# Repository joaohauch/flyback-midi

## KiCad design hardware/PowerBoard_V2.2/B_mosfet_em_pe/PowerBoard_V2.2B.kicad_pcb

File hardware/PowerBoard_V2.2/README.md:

# PowerBoard V2.2: placa de potência fresada (face simples)

É a PowerBoard V2.1 (totem pole) com as correções da V3.6, montada no desenho da PowerBoard V3 do EasyEDA:

- o tamanho é o mesmo, 85,2 × 39,5 mm;
- as peças de potência estão nas mesmas posições;
- saíram o FOD3184, o 7815 e os capacitores de 15 V;
- o gate é acionado pelo totem pole BC337/BC327, alimentado com os 12 V que vêm da placa de controle.

O nome é V2.2 porque já existe uma `PowerBoardV2_1.schdoc` no Altium: é o totem pole com zener, 22 Ω e IRFP260N.

## Duas versões

| Pasta | IRFP264N | Para quê |
|---|---|---|
| `A_mosfet_embaixo/` (V2.2A) | Deitado **embaixo** da placa, com a aba no dissipador que serve de base do conjunto | A ideia principal |
| `B_mosfet_em_pe/` (V2.2B) | Em pé na face de cima, com a aba virada para a borda de baixo | Reserva, se a A não der certo |

Muda pouco entre as duas:

- **O mesmo:** tamanho, todas as outras peças e quase todo o cobre.
- **Pads do IRFP264N:** ficam no mesmo lugar, mas trocam o gate e o source de lado. Na A a ordem é G-D-S da esquerda para a direita; na B, S-D-G.
- **Fio JP1:** sempre passa por cima do dreno, mas leva coisas diferentes:
  - na **A**, o terra do driver até o source, que fica do outro lado do dreno;
  - na **B**, o gate até o MOSFET. O source fica do lado do driver e é ligado por trilha.

## Arquivos

| Arquivo | O que é |
|---|---|
| `gerar_v22.py` | Gera as duas versões: `python gerar_v22.py` (ou só uma: `python gerar_v22.py B`). |
| `pcb_v22.py` | Posições, trilhas, zonas e textos. Roda no Python do KiCad; o `gerar_v22.py` chama. |
| `FBMD.pretty/` | Footprints para fresar, comuns às duas versões. |
| `<versão>/PowerBoard_V2.2X.kicad_pro`, `.kicad_sch`, `.kicad_pcb`, `.kicad_dru` | Projeto do KiCad 10. ERC e DRC sem erros, DRC com paridade de esquema. O `.kicad_dru` põe 1,5 mm entre +24V e GND. |
| `<versão>/*_impressao_topo.png`, `*_cobre.png`, `*_3d_*.png` | Prévias. |

Para mudar a placa, edite o `gerar_v22.py` (esquema e footprints) ou o `pcb_v22.py` (layout) e rode de novo. Mexer no KiCad à mão também funciona, mas a próxima geração sobrescreve.

Gerar de novo pede o KiCad 10 e a pasta do projeto inteira, não só o repositório: o `gerar_v22.py` usa a biblioteca `FlybachSimulations/lib/kicad_sch.py` e o modelo `FlybachSchems/FlybachSchems.kicad_pro`, que ficam fora do git, e os acha subindo pastas a partir de onde está. Para só abrir no KiCad ou mandar para a fresa, esta pasta basta.

Em `<versão>/fabricacao/` fica só o que a fresa pede, todos com a origem (0, 0) no canto inferior esquerdo da placa. Os mesmos quatro arquivos estão em `<versão>/PowerBoard_V2.2X_fresa.zip`, pronto para enviar:

- `*-B_Cu.gbr`: o cobre, só com pads, trilhas e áreas, sem texto (menos tempo de fresa). É o único cobre, porque a placa é de face simples. Fica embaixo, mas o arquivo está desenhado visto de cima, como todo Gerber.
- `*-Edge_Cuts.gbr`: o contorno.
- `*-PTH.drl`: os furos das peças (Excellon, em mm).
- `*-NPTH.drl`: os 4 furos M3 de fixação.

Na pasta da versão ficam também:

- `*_impressao_topo.pdf`: a serigrafia em cores, para colar por cima (próxima seção).
- `*_cobre_visto_de_baixo.pdf`: o cobre espelhado, como fica na placa. Na A, mostra também o contorno do MOSFET deitado.

## Serigrafia impressa

O `*_impressao_topo.pdf` desenha a face de cima como numa placa industrial: máscara verde, serigrafia branca, pads dourados e furos pretos. Traz a referência e o valor de cada peça e as marcas de polaridade. São seis cópias em tamanho real numa folha A4, para quatro placas e duas de reserva.

1. Imprima em **100 %** (tamanho real, sem "ajustar à página") e confira a régua de 50 mm com uma régua de verdade.
2. Recorte na linha da borda e cole sobre a face de cima, com cola em bastão ou fita dupla-face fina, alinhando pelos furos.
3. Fure o papel nos furos pretos com uma agulha, ou deixe as próprias pernas furarem. Uma fita transparente por cima protege o papel do fluxo de solda.

Os valores de Q1, Q2 e D1 estão na legenda do canto de baixo à esquerda; ao lado de cada peça não cabiam.

## No FlatCAM

1. **Espelhar.** Abra o cobre, o contorno e os furos. Espelhe os três juntos no eixo Y, com a ferramenta *2-Sided PCB* e o contorno como caixa de referência. O cobre é cortado com a placa virada para baixo.
2. **Isolação.** A folga é de 1,5 mm em volta do dreno e entre o +24V e o GND; no resto, de 0,5 mm ou mais. Com poucas passadas, sobra uma tira de cobre solta no meio das folgas de 1,5 mm. Use passadas suficientes para limpar 1,5 mm, ou rode *NCC* nessas regiões.
3. **Furos.** São 51 furos em seis diâmetros:

   | Broca | Furos | Peças |
   |---|---|---|
   | 0,8 mm | 16 | resistores, diodo, BC, C7, 47 µF |
   | 1,0 mm | 14 | MKP, P2, JP1 |
   | 1,2 mm | 10 | eletrolíticos do banco, MUR860 |
   | 1,6 mm | 5 | IRFP264N, borne do primário |
   | 3,2 mm | 4 | H1 a H4, fixação nos standoffs (M3) |
   | 4,5 mm | 2 | XT60 |

   Os furos de 3,2 e 4,5 mm podem ser fresados com uma fresa menor.

## Montagem (as duas versões)

- **XT60:** o lado chanfrado é o GND, como na V3.
- **P2:** Molex KK de 3 vias, com 12V, GND e SIN nessa ordem, de cima para baixo. É a mesma ordem do J3 do controle.
- **J3:** borne de encaixe de 5,08 mm (2EDG), onde vai o primário. O pino de cima é +24V e o de baixo é o dreno.
- **C8 a C10:** cada um tem dois furos para a perna do dreno, um para o lote de passo 10 mm e outro para o de 15 mm.
- **JP1:** fio rígido por cima da placa, entre os dois furos a 16 mm. Na versão A, também serve para prender a garra do osciloscópio.
- **Pad quadrado é o pino 1:** o + dos eletrolíticos, o catodo dos diodos, o gate do MOSFET e o coletor dos BC.
- **Furos H1 a H4 (M3):** para os standoffs de nylon. O de cima à esquerda fica entre o XT60 e o C1, porque o canto é do XT60. O H3, embaixo à direita, fica no cobre do dreno: o cobre está a 1,5 mm do furo, mas use parafuso de nylon ali.
- **MUR860:** em pé, com a aba para o lado do banco, como na V3.
- **Aba do IRFP264N = dreno:** chega a ~230–250 V em pulsos. Ponha uma isolação entre a aba e o dissipador (mica ou silicone, com bucha isolante no parafuso). Sem ela, o dissipador vira dreno.

### Versão A: MOSFET embaixo

Para os pinos caírem certo nos pads:

- o corpo deita **para dentro da placa**, embaixo do MUR860 e do C2;
- a face escrita fica virada para a placa e a aba vai no dissipador;
- as pernas saem para o lado da borda de baixo e sobem dobradas a 90° para os furos;
- assim a ordem é G-D-S como nos pads. Deitado para fora da placa, G e S trocariam.

O "G" da serigrafia marca o gate. A montagem pede ainda:

- **Fixação:** o furo do MOSFET fica embaixo do C2. Prenda pelo lado do dissipador (parafuso por baixo, porca do lado do MOSFET) ou com uma presilha.
- **Standoffs:** de ~10 mm. Cabem o MOSFET (5 mm), a isolação e as pontas das soldas da placa; as pernas do TO-247 (~20 mm) dão para a dobra.

### Versão B: MOSFET em pé

- **Posição:** o IRFP264N fica em pé, com a aba virada para a borda de baixo. O gate fica à direita, do lado dos MKP, e está marcado com "G" na serigrafia.
- **Dissipador:** vai preso na aba, do lado da borda. Ele passa por cima da parte de baixo da placa e pode sair para fora dela.
  - Se for mais largo que ~17 mm, fica por cima do D1 e do R1: deixe-o suspenso, sem encostar na placa.
- **Fio JP1:** leva o gate por cima do dreno. Deixe-o curto e rente à placa.

## Lista de peças

| Ref | Peça |
|---|---|
| C1 a C4 | 470 µF 35 V, 12,5 mm, passo 5 mm |
| C6 | 47 µF 25 V, 6,3 mm, passo 2,5 mm |
| C7 | 100 nF cerâmico, passo 5 mm |
| C8 a C10 | 100 nF MKP, 400 V DC (250/275 VAC) |
| D1 | 1N4148 |
| D2 | MUR860 |
| J1 | XT60 macho para PCB |
| J3 | borne de encaixe 5,08 mm, 2 vias (2EDG) |
| JP1 | fio rígido de até 0,8 mm |
| P2 | Molex KK 254, 3 vias |
| Q1, Q2 | BC337, BC327 |
| Q3 | IRFP264N |
| R1 | 10 Ω, 1/4 W |
| R2 | 10 kΩ, 1/4 W |
| H1 a H4 | standoffs e parafusos M3 de nylon |

## O que mudou da V3 do EasyEDA

- **Driver.** Saiu o driver isolado: FOD3184, 7815, CN1, R3, os capacitores de 15 V e o jumper que levava os 24 V ao 7815. Entrou o totem pole, alimentado pelos 12 V do controle.
- **Gate.** 10 Ω em paralelo com o 1N4148 (antes 22 Ω), e 10 kΩ para o GND.
- **Cerâmico do 24 V.** Não há mais. O 100 nF da V3 era o da entrada do 7815; a 40 kHz, ao lado de 1880 µF, ele não muda nada. Por isso não existe C5: as referências seguem as da V3.6, sem o C5 e sem o C11.
- **C11.** O C11 da V3.6 (quarto MKP, não montado) não entrou: não cabe sem apertar o driver, e com o PR5 o dreno já baixa.
- **+24V e GND.** A folga entre os dois é de 1,5 mm (antes 0,6 mm). Eles correm lado a lado pela placa toda, e uma rebarba da fresa ou um respingo de solda curtaria a fonte. Os pads do XT60 são ovais, para dar 1,6 mm entre os pinos.
- **Furos.** 1,6 mm no TO-247 e no borne; antes eram rasgos de 1,0 × 1,8 mm e furos de 1,7 mm. Entraram quatro furos M3 para os standoffs; a V3 não tinha.
- **Texto no cobre.** Não há: a serigrafia vai impressa e colada por cima.
- **XT60.** Na V3.6, o J1.1 era o +24V. Aqui o pino 1 é o GND, que é o lado chanfrado do XT60.

O Gerber original da V3 está em `FlybachSchems/PowerBoardV3_EasyEDA/`, fora do repositório: é a versão com o FOD3184, que não vai ser fabricada agora.

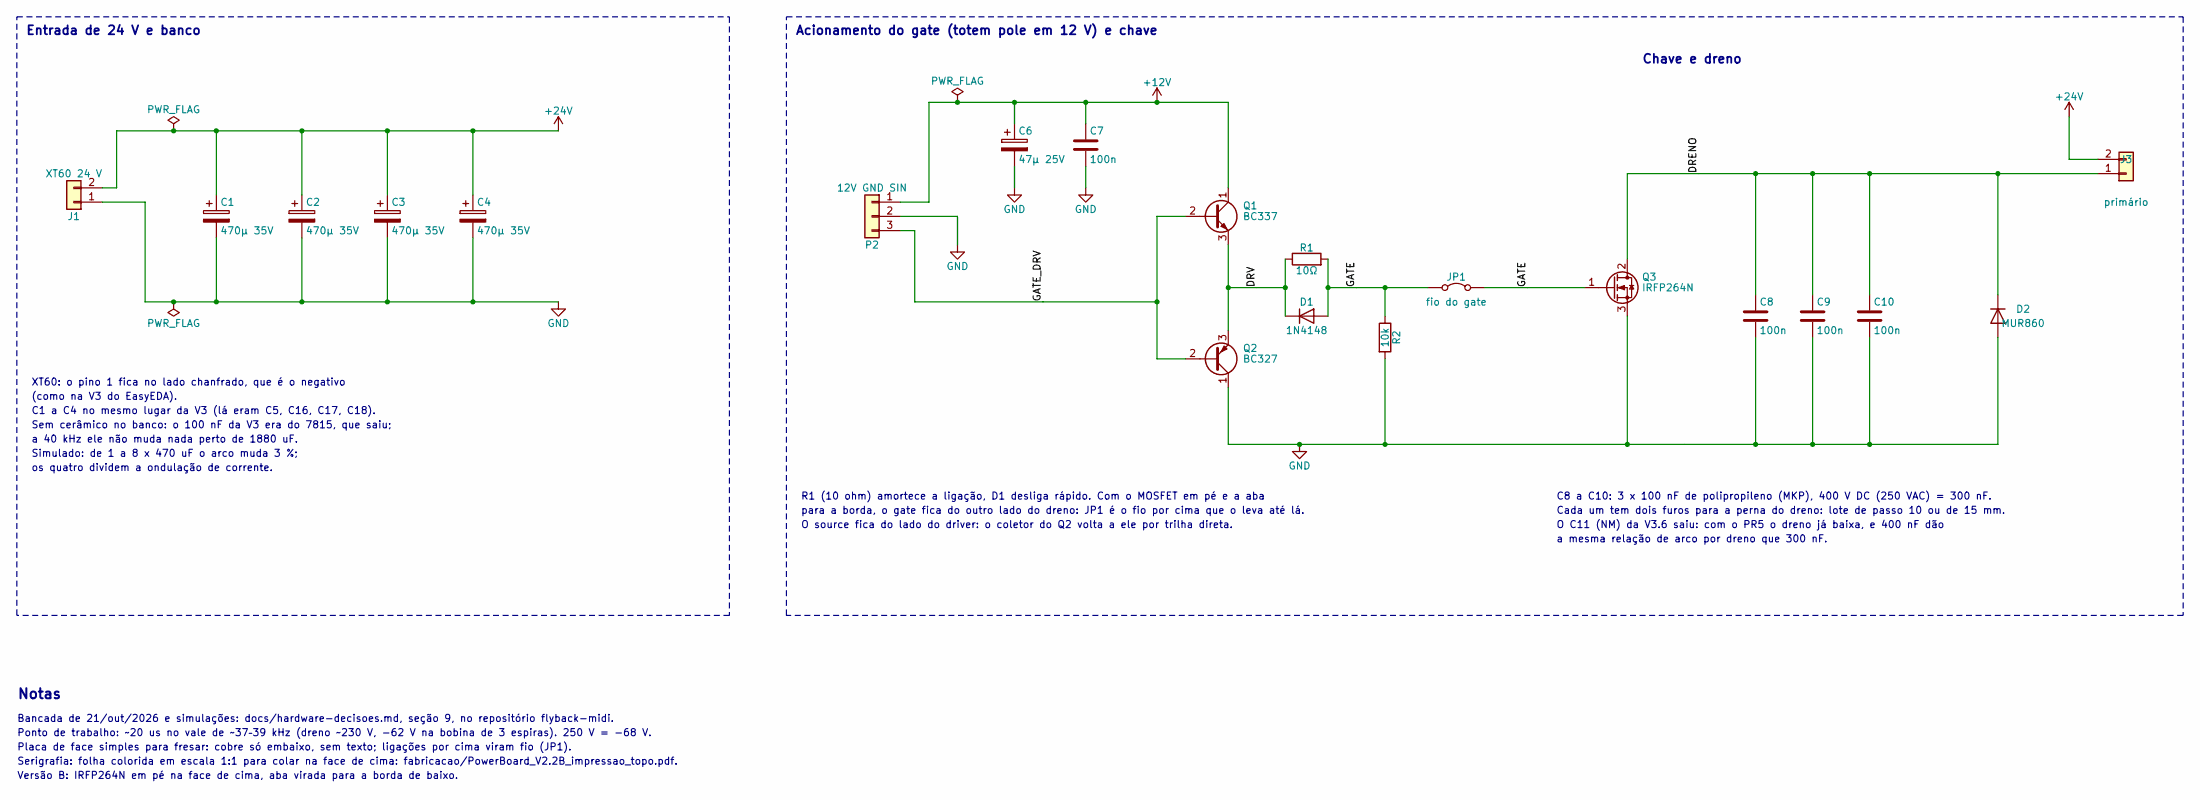
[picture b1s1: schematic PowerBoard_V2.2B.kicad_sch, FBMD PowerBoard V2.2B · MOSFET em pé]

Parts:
C1, C2, C3, C4: 470µ 35V; CP_Radial_D12.5_P5.00_CNC
C6: 47µ 25V; CP_Radial_D6.3_P2.50_CNC
C7: 100n; C_Disc_P5.00_CNC
C8, C9, C10: 100n; C_MKP_W6_P10_P15_CNC
D1: 1N4148; D_DO-35_P7.62_CNC
D2: MUR860; TO-220-2_Vertical_CNC
J1: XT60 24 V; XT60-M_Vertical_CNC
J3: primário; Phoenix_MCV_1x02_P5.08_CNC
JP1: fio do gate; Jumper_Fio_16.0mm
P2: 12V GND SIN; Molex_KK-254_1x03_CNC
Q1: BC337; TO-92_Inline_Wide_CNC
Q2: BC327; TO-92_Inline_Wide_CNC
Q3: IRFP264N; TO-247-3_Vertical_CNC
R1: 10Ω; R_Axial_P10.16_CNC
R2: 10k; R_Axial_P10.16_CNC

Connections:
+12V: C6.1, C7.1, P2.1, Q1.1 (C)
+24V: C1.1, C2.1, C3.1, C4.1, J1.2, J3.2
/DRENO: C8.1, C9.1, C10.1, D2.1 (K), J3.1, Q3.2 (D)
/DRV: D1.1 (K), Q1.3 (E), Q2.3 (E), R1.1
/GATE: D1.2 (A), JP1.1 (A), JP1.2 (B), Q3.1 (G), R1.2, R2.1
/GATE_DRV: P2.3, Q1.2 (B), Q2.2 (B)
GND: C1.2, C2.2, C3.2, C4.2, C6.2, C7.2, C8.2, C9.2, C10.2, D2.2 (A), J1.1, P2.2, Q2.1 (C), Q3.3 (S), R2.2

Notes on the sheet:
Entrada de 24 V e banco
XT60: o pino 1 fica no lado chanfrado, que é o negativo
(como na V3 do EasyEDA).
C1 a C4 no mesmo lugar da V3 (lá eram C5, C16, C17, C18).
Sem cerâmico no banco: o 100 nF da V3 era do 7815, que saiu;
a 40 kHz ele não muda nada perto de 1880 uF.
Simulado: de 1 a 8 x 470 uF o arco muda 3 %;
os quatro dividem a ondulação de corrente.
Acionamento do gate (totem pole em 12 V) e chave
Chave e dreno
R1 (10 ohm) amortece a ligação, D1 desliga rápido. Com o MOSFET em pé e a aba
para a borda, o gate fica do outro lado do dreno: JP1 é o fio por cima que o leva até lá.
O source fica do lado do driver: o coletor do Q2 volta a ele por trilha direta.
C8 a C10: 3 x 100 nF de polipropileno (MKP), 400 V DC (250 VAC) = 300 nF.
Cada um tem dois furos para a perna do dreno: lote de passo 10 ou de 15 mm.
O C11 (NM) da V3.6 saiu: com o PR5 o dreno já baixa, e 400 nF dão
a mesma relação de arco por dreno que 300 nF.
Notas
Bancada de 21/out/2026 e simulações: docs/hardware-decisoes.md, seção 9, no repositório flyback-midi.
Ponto de trabalho: ~20 us no vale de ~37–39 kHz (dreno ~230 V, -62 V na bobina de 3 espiras). 250 V = -68 V.
Placa de face simples para fresar: cobre só embaixo, sem texto; ligações por cima viram fio (JP1).
Serigrafia: folha colorida em escala 1:1 para colar na face de cima: fabricacao/PowerBoard_V2.2B_impressao_topo.pdf.
Versão B: IRFP264N em pé na face de cima, aba virada para a borda de baixo.

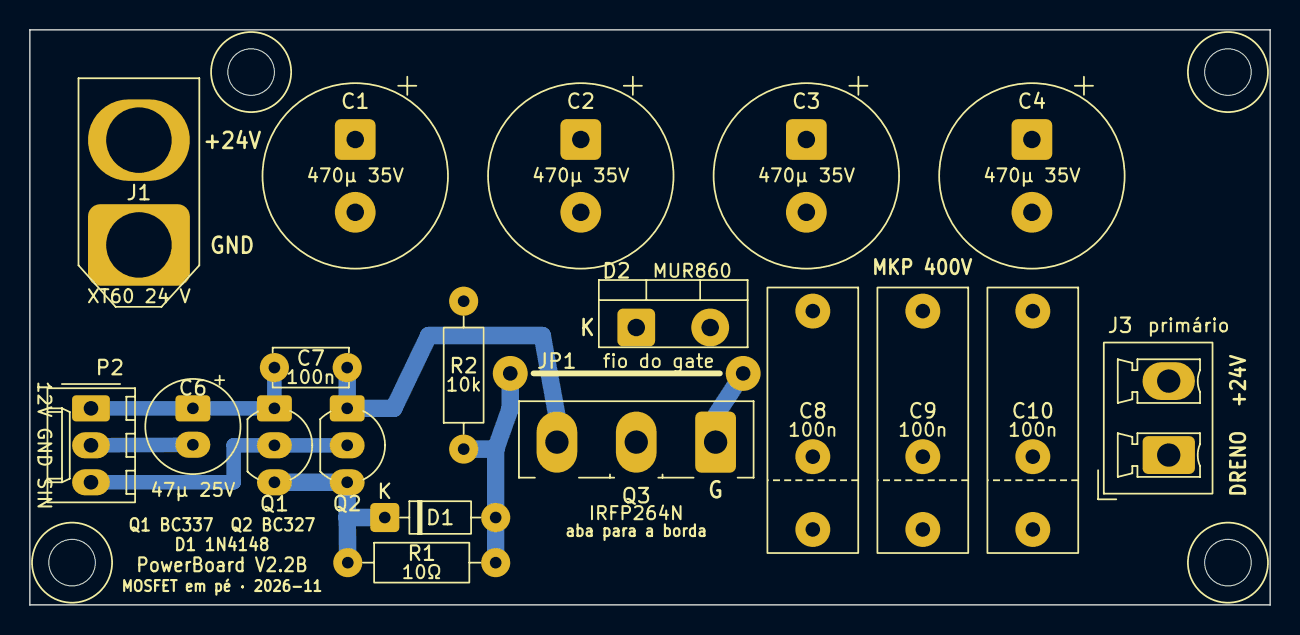
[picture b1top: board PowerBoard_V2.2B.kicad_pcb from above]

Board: 2 copper layers, 85.2 x 39.5 mm, 24 parts (0 on the bottom side), 7 nets.

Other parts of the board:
H1, H2, H3, H4: M3; Furo_M3_CNC
